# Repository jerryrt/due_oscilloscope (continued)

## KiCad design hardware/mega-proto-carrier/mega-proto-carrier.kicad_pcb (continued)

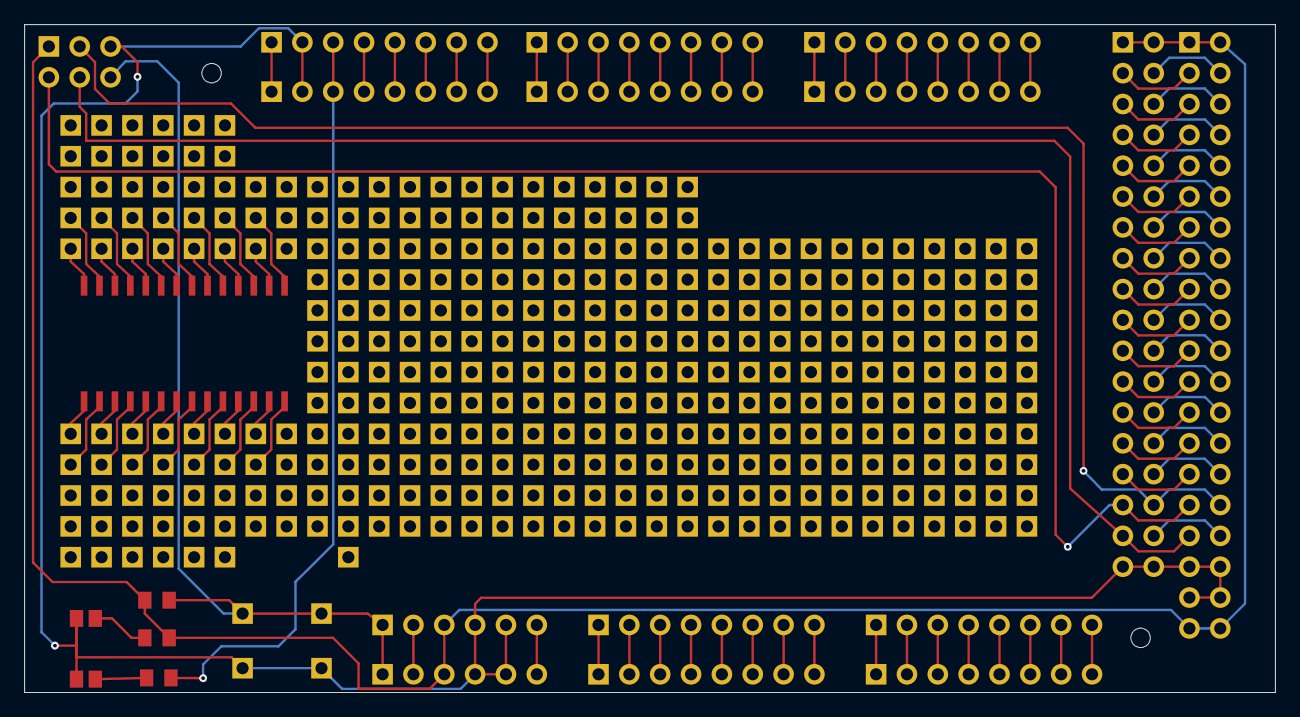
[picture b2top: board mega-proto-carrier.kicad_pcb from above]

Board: 2 copper layers, 103.0 x 55.0 mm, 25 parts (0 on the bottom side), 106 nets.

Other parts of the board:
H1, H2: Hole_estimate_1.6mm

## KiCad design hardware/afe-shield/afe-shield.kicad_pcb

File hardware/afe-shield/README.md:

# AFE shield

Stage A schematic for the Arduino Due analog front end. Verified with
KiCad 10.0.6 and ngspice 47. **KiCad 10.x is the default and required CAD
major version on every team/bench.** Do not edit or validate this project
with KiCad 9 or older. **Design/prototype only: not ready for
fabrication.** See [review findings](REVIEW.md), [requirements](../../docs/afe.md)
and [official references](../../docs/reference/README.md).

For the end-to-end process, read
[AFE design with KiCad: workflow and quality gates](../../docs/afe-workflow.md).
The [physical-build checklist](BUILD-VALIDATION.md) covers hand-wiring,
two-layer layout, fit and the measurements that only assembly can establish.
For the low-cost socketed experiment, use the self-contained
[Stage A prototype recipe](../../docs/afe-prototype.md). It specifies a
PDIP package for the hand build only, leaves this SOIC CAD design unchanged,
and keeps JP1 open on an unmodified Due.

For the **physical proto shield in the supplied photographs**, open the separate
[Mega PrototypeShield V3 carrier project](../mega-proto-carrier/README.md).
It records the measured 103 x 55 mm carrier, its pad grid and contact
inventory. Its photo-derived geometry and unverified hidden copper are
distinct from the AFE circuit and custom-board template in this directory.

| file | what |
|---|---|
| `afe-shield.kicad_pro`, `afe-shield.kicad_sch` | project and root sheet: Mega-format mechanics with Due-specific net assignments |
| `reference.kicad_sch` | Stage A: the LM4040 reference, its buffer, the mid-rail, the AREF jumper |
| `pin-driver.kicad_sch` | Stage A: the followers from DAC0 and DAC1 into A0 and A1, VREF1V5 onto A2, the unused pins held |
| `afe-shield.kicad_pcb` | the template's board outline, headers and holes; the PCB phase draws on it |
| `models/afe-models.lib` | pin-order adapters for the original Microchip and TI models in `models/vendor/` |
| `sim/sources.cir` | simulation-only Due supplies, DAC stimuli and AREF load; included by root schematic text |
| `sim/stage_a.cir`, `sim/run.sh` | DC, AC, settling and reference-load checks using the exported schematic |
| `stage-a.wbk` | KiCad operating-point analysis setup |
| `check.py` | ERC and critical connector/analog-net regression checks |
| `sim/screen.py`, `sim/README.md` | Acquisition-load and driver sensitivity screening, model assumptions and evaluation candidates |

## Finding D1 and the Phase A IC

Open **afe-shield.kicad_pro**, then its Schematic Editor, not the PCB Editor.
Enter the **reference** sheet by double-clicking its rectangle on the root
sheet. **D1** is at the upper left, below R1: the LM4040 3.0 V shunt reference.
Its label is horizontal and readable. Find (`Cmd+F` on macOS) can search D1;
enable searching all sheets when searching from the root.

**U1 is one physical MCP6024 quad IC**, drawn as five units:

| unit | sheet | function |
|---|---|---|
| U1A | reference | 3.0 V reference buffer |
| U1B | reference | 1.5 V mid-rail buffer |
| U1E | reference | supply pins 4 and 11, with C4 decoupling |
| U1C | pin-driver | DAC0 follower into A0 |
| U1D | pin-driver | DAC1 follower into A1 |

D1 and U1 are not on the PCB yet. It contains the template headers and
mounting holes only; their absence there is not a search problem.

## Running the checks

From the repository root:

```sh
python3 hardware/afe-shield/check.py
hardware/afe-shield/sim/run.sh
hardware/afe-shield/sim/run.sh --strict
python3 hardware/afe-shield/sim/screen.py
```

Requires Python 3, KiCad 10.x `kicad-cli` and `ngspice`. Both check scripts
reject a different KiCad major version before exporting or checking files.
The runner discovers the macOS
KiCad app automatically, or accepts `KICAD_CLI` / `NGSPICE` executable paths.
When multiple KiCad installations exist, set `KICAD_CLI` explicitly to the
10.x executable and open the project in the corresponding GUI. Use matching
10.x symbol/footprint libraries; record the exact patch version with results.
Some source files retain KiCad 9 serialization until saved by KiCad 10;
their generator tags are provenance, not the supported toolchain version.
Generated netlists, logs and numeric `.dat` traces stay in `sim/` and are
ignored by Git. Exit zero means the analyses completed and basic reference
sanity checks passed; **REVIEW messages are unresolved performance targets**.
Use `--strict` to make those baseline REVIEW findings return exit 2.
The separate screen records diagnostic outcomes without claiming a release
gate; see [its method and limitations](sim/README.md).

In KiCad, open **Inspect → Simulator → File → Open Workbook**, choose
`stage-a.wbk`, and run the operating-point analysis. In **Simulation → Edit
Analysis Tab**, choose **PSpice** compatibility and keep **Add full path for
.include library directives** enabled. This setup was run in the GUI as well
as from the command line. Create further tabs with **Simulation → New Analysis
Tab**: AC (decade, 100 points, 1 kHz to 100 MHz), or transient (2 ns, 40 us).
Plot `V(a0)`, `V(dac0)`, `V(buffer)` and `V(vref3v0)` as appropriate.

The GUI defaults to the nominal static AREF load. The batch deck additionally
sets `AREF_C=200n` and reruns the load-step stress test. Supplies and test loads
are simulation-only, never physical PCB parts.

**JP1 stays open by default.** Do not close it on a Due with JR1 still fitted.
The alternative AREF connection requires the documented Due modification and
reference-load stability validation; see the review before wiring hardware.

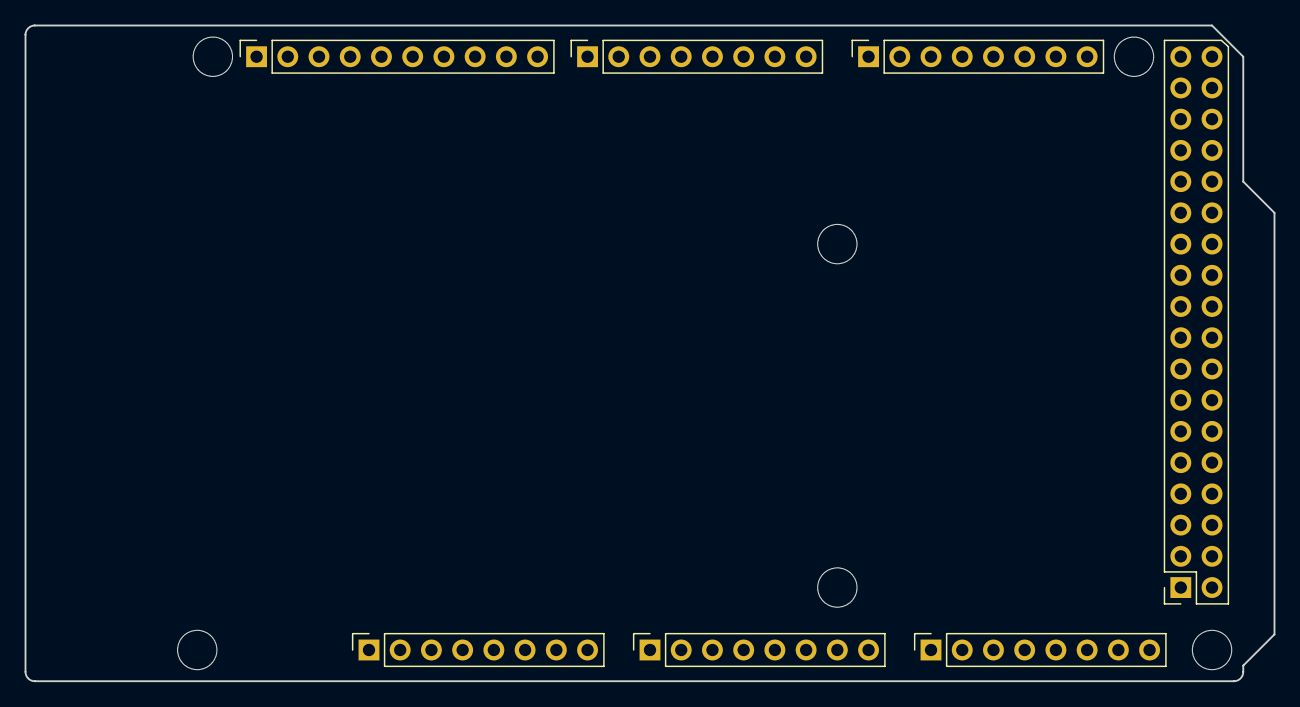
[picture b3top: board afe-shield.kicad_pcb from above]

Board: 2 copper layers, 101.6 x 53.3 mm, 13 parts (0 on the bottom side), 2 nets, no tracks yet.

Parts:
J1: Power; PinSocket_1x08_P2.54mm_Vertical
J2: PWM; PinSocket_1x10_P2.54mm_Vertical
J3, J5: Analog; PinSocket_1x08_P2.54mm_Vertical
J4: PWM; PinSocket_1x08_P2.54mm_Vertical
J6: Communication; PinSocket_1x08_P2.54mm_Vertical
J7: Digital; PinSocket_2x18_P2.54mm_Vertical
MH1, MH2, MH3, MH4, MH5, MH6: MountingHole_3.2mm

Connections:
+5V: J1.5, J7.35, J7.36
GND: J1.6, J1.7, J2.4, J7.1, J7.2

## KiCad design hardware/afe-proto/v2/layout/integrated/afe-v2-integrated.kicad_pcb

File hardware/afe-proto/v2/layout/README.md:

# v2 layout WIP (not for main)

power/        power4_step_<cap>.kicad_pcb (one per moved cap, in the order C403 C402 C401 C404 C407 C408 C406), power4_final, power3_final (baseline)
v2-blocks/    inputs copied from the v2 worktree (BASE, AWG/REFCAL/SCOPE-east finals) and power/ tooling; power/scratch/try.sh = move + reroute + check
v2-integration/  integrate.sh (merge, corridors, DRC, verify) with POWER_BOARD=...; figs.py, fence4.py
integrated/   afe-v2-integrated.kicad_pcb (power4), ref_power3/ (same pipeline with power3_final), render/, drc_full.json
Run everything in the image: docker/pcb/run.sh -m 3G -t 600 bash /work/hardware/afe-proto/v2/layout/v2-integration/integrate.sh

LR-11 on the integrated board (`--config v2_layout`, `pcbtools/boards/v2_layout.py`):
outlines.py            the one table of block outlines (Due mm) the silk is drawn from and the config reads, with SHARED_PARTS (U101 is held to CH1)
outlines_from_silk.py  recovers the outlines actually drawn on a board's F.Silkscreen (dashed or broken sides included); `--check` compares them with the table
draw_outlines.py       adds the table's rectangles the silk lacks (the AWG BNC outline); silk only
silk labels            pcbtools/silkplace.py, silkapply.py, silkruns.py (runs and renumbering), silkbom.py (the dense blocks' leftovers to the BOM: SILK_TO_BOM), bncframe.py (the BNCs); silkread (pcbtools/silkread.py) is the one judge of where a label may sit (D30, docs/afe.md); the earlier place_designators.py / refine_designators.py and the LR-11 pair-gap, one-label, foreign-outline and distance rules are retired
set_models.py          points U401 at the project's VRML stand-in for the WSON-12 (MODEL_BY_REF in boards/v2_layout.py); text splice, idempotent; render only, a STEP export leaves it out
place_bncs.py          puts the three BNCs where boards/v2_layout.py says (BNC_X, BNC_Y, SCOPE_PITCH: CH1 44.45, CH2 26.67, AWG 8.89, Due mm; owner 2026-11-13) and moves what hangs on them: labels, silk boxes, the two scope input runs (pad, jog inside the BNC fence, old corridor), J605's designator (DESIGNATOR_AT); text splice, idempotent; refill the zones afterwards
refill_zones.py        refills every zone with pcbnew so the fills honour the project's min_copper_edge_clearance (0.45); splices only the filled_polygon blocks into the board text; idempotent; run in the image
pinlabels (pcbtools/pinlabels.py)  the Due's own pin names beside each edge-row socket, on top silk in the bands (LR-11): python3 -m pcbtools.pinlabels BOARD --config v2_layout --write; --check and --list too. Names come from docs/due-header-table.md, sockets from EDGE_SOCKETS in boards/v2_layout.py
Both tools above are pure text editing except place_designators.py, which reads the board with pcbnew.

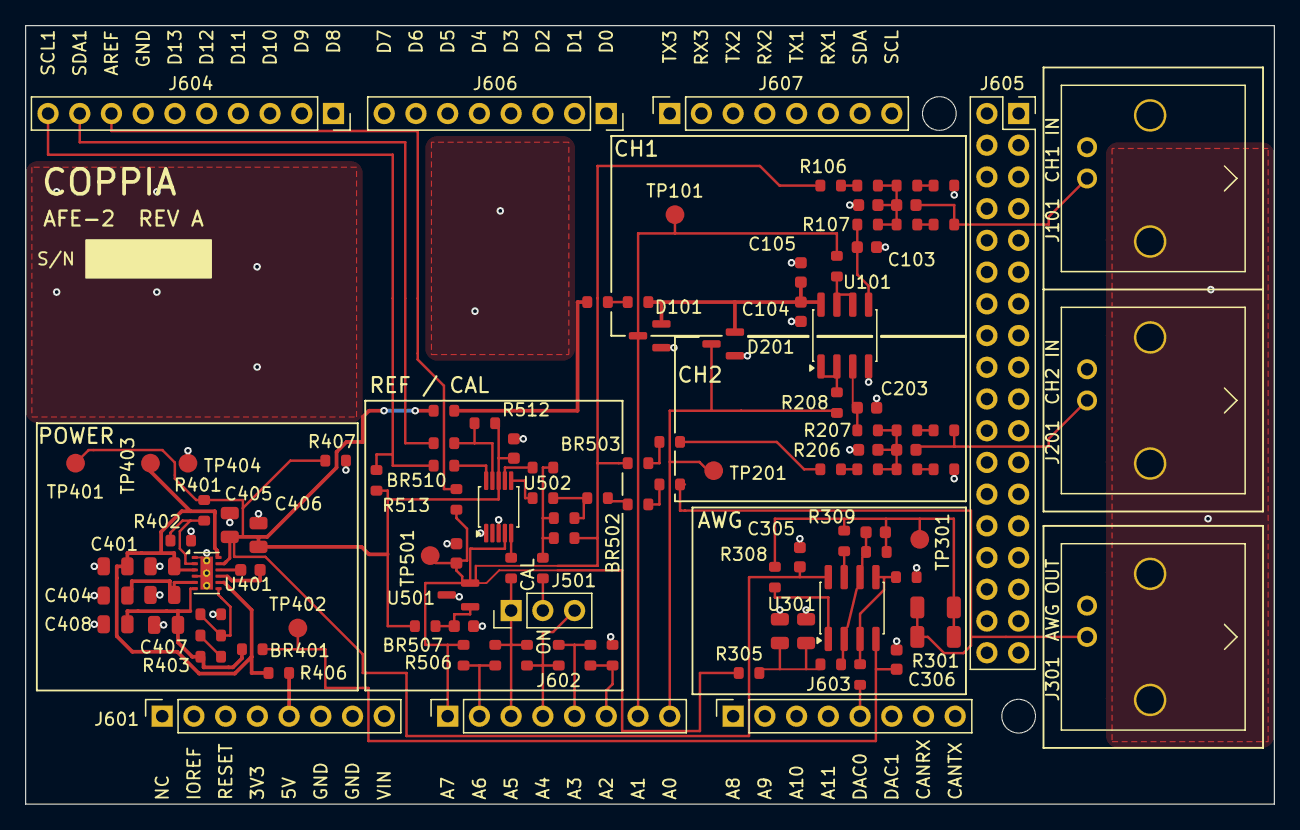
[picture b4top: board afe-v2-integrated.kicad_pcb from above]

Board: 2 copper layers, 100.0 x 62.3 mm, 112 parts (0 on the bottom side), 61 nets.

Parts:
BR101, BR102, BR401, BR501, BR502, BR503, BR504, BR506, BR507, BR508, BR509, BR510, BR511: 0R; R_0603_1608Metric
C101, C201: 18p C0G; C_0603_1608Metric
C102, C202: 47p C0G; C_0603_1608Metric
C103, C203, C301: 10p C0G; C_0603_1608Metric
C104, C305, C306, C502, C503: 100n X7R; C_0603_1608Metric
C105, C409, C501: 1u X5R; C_0603_1608Metric
C303, C304, C401, C402, C403, C404, C405, C406, C407, C408: 10u X5R 25V; C_0805_2012Metric
D101, D201: BAV99; SOT-23
J101, J201, J301: KH-BNC50-3511; BNC_Kinghelm_KH-BNC50-3511_Horizontal
J501: CAL; PinHeader_1x03_P2.54mm_Vertical
J601: POWER0; PinSocket_1x08_P2.54mm_Vertical
J602: ADCL0; PinSocket_1x08_P2.54mm_Vertical
J603: ADCH0; PinSocket_1x08_P2.54mm_Vertical
J604: PWMH0; PinSocket_1x10_P2.54mm_Vertical
J605: XIO0; PinSocket_2x18_P2.54mm_Vertical_DueXIO
J606: PWML0; PinSocket_1x08_P2.54mm_Vertical
J607: COMMUNICATION0; PinSocket_1x08_P2.54mm_Vertical
MH601, MH602: M2.5 standoff; MountingHole_2.7mm_M2.5
R101, R103, R201, R203: 470k 1%; R_0603_1608Metric
R102, R202: 300k 1%; R_0603_1608Metric
R104, R105, R204, R205: 330k 1%; R_0603_1608Metric
R106, R206, R514: 0R; R_0603_1608Metric
R107, R207: 470R 1%; R_0603_1608Metric
R108, R208: 22R 1%; R_0603_1608Metric
R301, R302: 100R 1%; R_1206_3216Metric
R303, R304, R306: 3k 1%; R_0603_1608Metric
R305: 150R 1%; R_0603_1608Metric
R307: 27k 1%; R_0603_1608Metric
R308, R309, R406: 1R 1%; R_0603_1608Metric
R401: 120k 1%; R_0603_1608Metric
R402: 68k 1%; R_0603_1608Metric
R403: 56k 1%; R_0603_1608Metric
R404: 8.2k 1%; R_0603_1608Metric
R405: 100k 1%; R_0603_1608Metric
R407: 1.8k 1%; R_0603_1608Metric
R501, R502, R503, R504, R505, R506: 330R 1%; R_0603_1608Metric
R507: 15k 1%; R_0603_1608Metric
R508, R511: 10k 1%; R_0603_1608Metric
R509: 1k 1%; R_0603_1608Metric
R510: 3.9k 1%; R_0603_1608Metric
R512, R513: 4.7k 1%; R_0603_1608Metric
TP101: A1; TestPoint_Pad_D1.5mm
TP201: A0; TestPoint_Pad_D1.5mm
TP301: AWG_OUT; TestPoint_Pad_D1.5mm
TP401: +3V3A; TestPoint_Pad_D1.5mm
TP402: VNEG; TestPoint_Pad_D1.5mm
TP403: +5V_F; TestPoint_Pad_D1.5mm
TP404: GND; TestPoint_Pad_D1.5mm
TP501: VREF; TestPoint_Pad_D1.5mm
U101, U301: TPH2502-SR; SOIC-8_3.9x4.9mm_P1.27mm
U401: LM27762DSSR; WSON-12-1EP_3x2mm_P0.5mm_EP1x2.65_ThermalVias
U501: REF3030EAIDBZR; SOT-23
U502: ADS1115IDGSR; MSOP-10_3x3mm_P0.5mm

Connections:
/+3V3A: BR507.2, BR509.1, C305.1, C405.1, C406.1, C503.1, R401.1, R407.1, R512.1, R513.1, TP401.1, U301.8, U401.11, U502.8
/+3V3A_K: BR102.1, BR509.2
/+3V3A_R: BR507.1, C502.1, U501.1
/+3V3A_S: BR101.1, BR102.2
/+3V3A_U: BR101.2, C104.1, C105.1, D101.2, D201.2, U101.8
/+5V_DUE: J601.5, R406.1
/+5V_F: C401.1, C402.1, R406.2, TP403.1, U401.3, U401.8, U401.12
/A0: D201.3, J602.8, R208.2, TP201.1
/A1: D101.3, J602.7, R108.2, TP101.1
/ADS_B: R511.2, U502.7
/ADS_TAP: R510.2, U502.6
/AREF: J604.8, R514.2
/AWG_BIN: R306.2, R307.1, U301.3, U301.5
/AWG_BNC: BR501.2, J301.1, R301.2, R302.2
/AWG_BNC_L: BR502.1, R507.1
/AWG_BNC_M: BR501.1, BR502.2
/AWG_FB: C301.2, R303.2, R304.1, U301.2, U301.6
/AWG_OA: R308.1, U301.1
/AWG_OB: R309.1, U301.7
/AWG_VO: C301.1, R301.1, R302.1, R303.1, R308.2, R309.2, TP301.1
/AWG_VREF: C303.1, C304.1, R304.2, R305.2
/CH1_IN: C101.1, J101.1, R101.1
/CH1_M1: R101.2, R102.1
/CH1_M2: R103.2, R104.1
/CH1_M3: R105.2, R106.1
/CH1_N: C101.2, C102.1, R102.2, R103.1, R105.1, R107.1
/CH1_NP: C103.1, R107.2, U101.5
/CH1_OUT: R108.1, U101.6, U101.7
/CH2_IN: C201.1, J201.1, R201.1
/CH2_M1: R201.2, R202.1
/CH2_M2: R203.2, R204.1
/CH2_M3: R205.2, R206.1
/CH2_N: C201.2, C202.1, R202.2, R203.1, R205.1, R207.1
/CH2_NP: C203.1, R207.2, U101.3
/CH2_OUT: R208.1, U101.1, U101.2
/DAC0: J603.5, R306.1
/GND: C102.2, C103.2, C104.2, C105.2, C202.2, C203.2, C303.2, C304.2, C305.2, C306.2, C401.2, C402.2, C403.2, C404.2, C405.2, C406.2, C407.2, C408.2, C501.2, C502.2, C503.2, D101.1, D201.1, J101.2, J201.2, J301.2, J601.6, J601.7, J604.7, J605.35, J605.36, R104.2, R204.2, R307.2, R402.2, R405.2, R407.2, R501.1, TP404.1, U101.4, U401.1, U401.4, U401.13, U501.3, U502.1, U502.3
/LM_C1N: C409.2, U401.9
/LM_C1P: C409.1, U401.10
/LM_CP: C403.1, C404.1, U401.5
/LM_FB3M: R403.2, R404.1
/LM_FBN: R404.2, R405.1, U401.7
/LM_FBP: R401.2, R402.1, U401.2
/SCL: BR510.1, J604.10, R513.2
/SCL_A: BR510.2, U502.10
/SDA: BR511.1, J604.9
/SDA_A: BR511.2, R512.2, U502.9
/SNS_B: BR508.1, J501.2
/SNS_B_N: BR508.2, R508.2, R509.1, R511.1
/SNS_T0: R507.2, R508.1, R510.1
/TAP1: J602.6, R501.2, R502.1
/TAP2: J602.5, R502.2, R503.1
/TAP3: J501.3, J602.4, R503.2, R504.1
/TAP4: BR506.1, J501.1, J602.3, R504.2, R505.1
/TAP4_A: BR506.2, U502.5
/TAP5: J602.2, R505.2, R506.1
/VNEG: BR401.2, C306.1, TP402.1, U301.4
/VNEG_G: BR401.1, C407.1, C408.1, R403.1, U401.6
/VREF: BR503.1, C501.1, J602.1, R106.2, R305.1, R506.2, R509.2, R514.1, TP501.1, U501.2, U502.4
/VREF_M: BR503.2, BR504.1
/VREF_P: BR504.2, R206.2

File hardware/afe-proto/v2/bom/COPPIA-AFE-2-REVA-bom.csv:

Comment,Designator,Footprint,LCSC Part #
"18p C0G","C101,C201","C_0603_1608Metric","C1647"
"47p C0G","C102,C202","C_0603_1608Metric","C1671"
"10p C0G","C103,C203,C301","C_0603_1608Metric","C1634"
"100n X7R","C104,C305,C306,C502,C503","C_0603_1608Metric","C14663"
"1u X5R","C105,C409,C501","C_0603_1608Metric","C15849"
"10u X5R 25V","C303,C304,C401,C402,C403,C404,C405,C406,C407,C408","C_0805_2012Metric","C15850"
"BAV99","D101,D201","SOT-23","C2500"
"470k 1%","R101,R103,R201,R203","R_0603_1608Metric","C23178"
"300k 1%","R102,R202","R_0603_1608Metric","C23024"
"330k 1%","R104,R105,R204,R205","R_0603_1608Metric","C23137"
"0R","R106,R206","R_0603_1608Metric","C21189"
"470R 1%","R107,R207","R_0603_1608Metric","C23179"
"22R 1%","R108,R208","R_0603_1608Metric","C23345"
"100R 1%","R301,R302","R_1206_3216Metric","C17901"
"3k 1%","R303,R304,R306","R_0603_1608Metric","C4211"
"150R 1%","R305","R_0603_1608Metric","C22808"
"27k 1%","R307","R_0603_1608Metric","C22967"
"1R 1%","R308,R309,R406","R_0603_1608Metric","C22936"
"120k 1%","R401","R_0603_1608Metric","C25808"
"68k 1%","R402","R_0603_1608Metric","C23231"
"56k 1%","R403","R_0603_1608Metric","C23206"
"8.2k 1%","R404","R_0603_1608Metric","C25981"
"100k 1%","R405","R_0603_1608Metric","C25803"
"1.8k 1%","R407","R_0603_1608Metric","C4177"
"330R 1%","R501,R502,R503,R504,R505,R506","R_0603_1608Metric","C23138"
"15k 1%","R507","R_0603_1608Metric","C22809"
"10k 1%","R508,R511","R_0603_1608Metric","C25804"
"1k 1%","R509","R_0603_1608Metric","C21190"
"3.9k 1%","R510","R_0603_1608Metric","C23018"
"4.7k 1%","R512,R513","R_0603_1608Metric","C23162"
"TPH2502-SR","U101,U301","SOIC-8_3.9x4.9mm_P1.27mm","C118223"
"LM27762DSSR","U401","WSON-12-1EP_3x2mm_P0.5mm_EP1x2.65_ThermalVias","C473398"
"REF3030EAIDBZR","U501","SOT-23","C54120492"
"ADS1115IDGSR","U502","MSOP-10_3x3mm_P0.5mm","C37593"
